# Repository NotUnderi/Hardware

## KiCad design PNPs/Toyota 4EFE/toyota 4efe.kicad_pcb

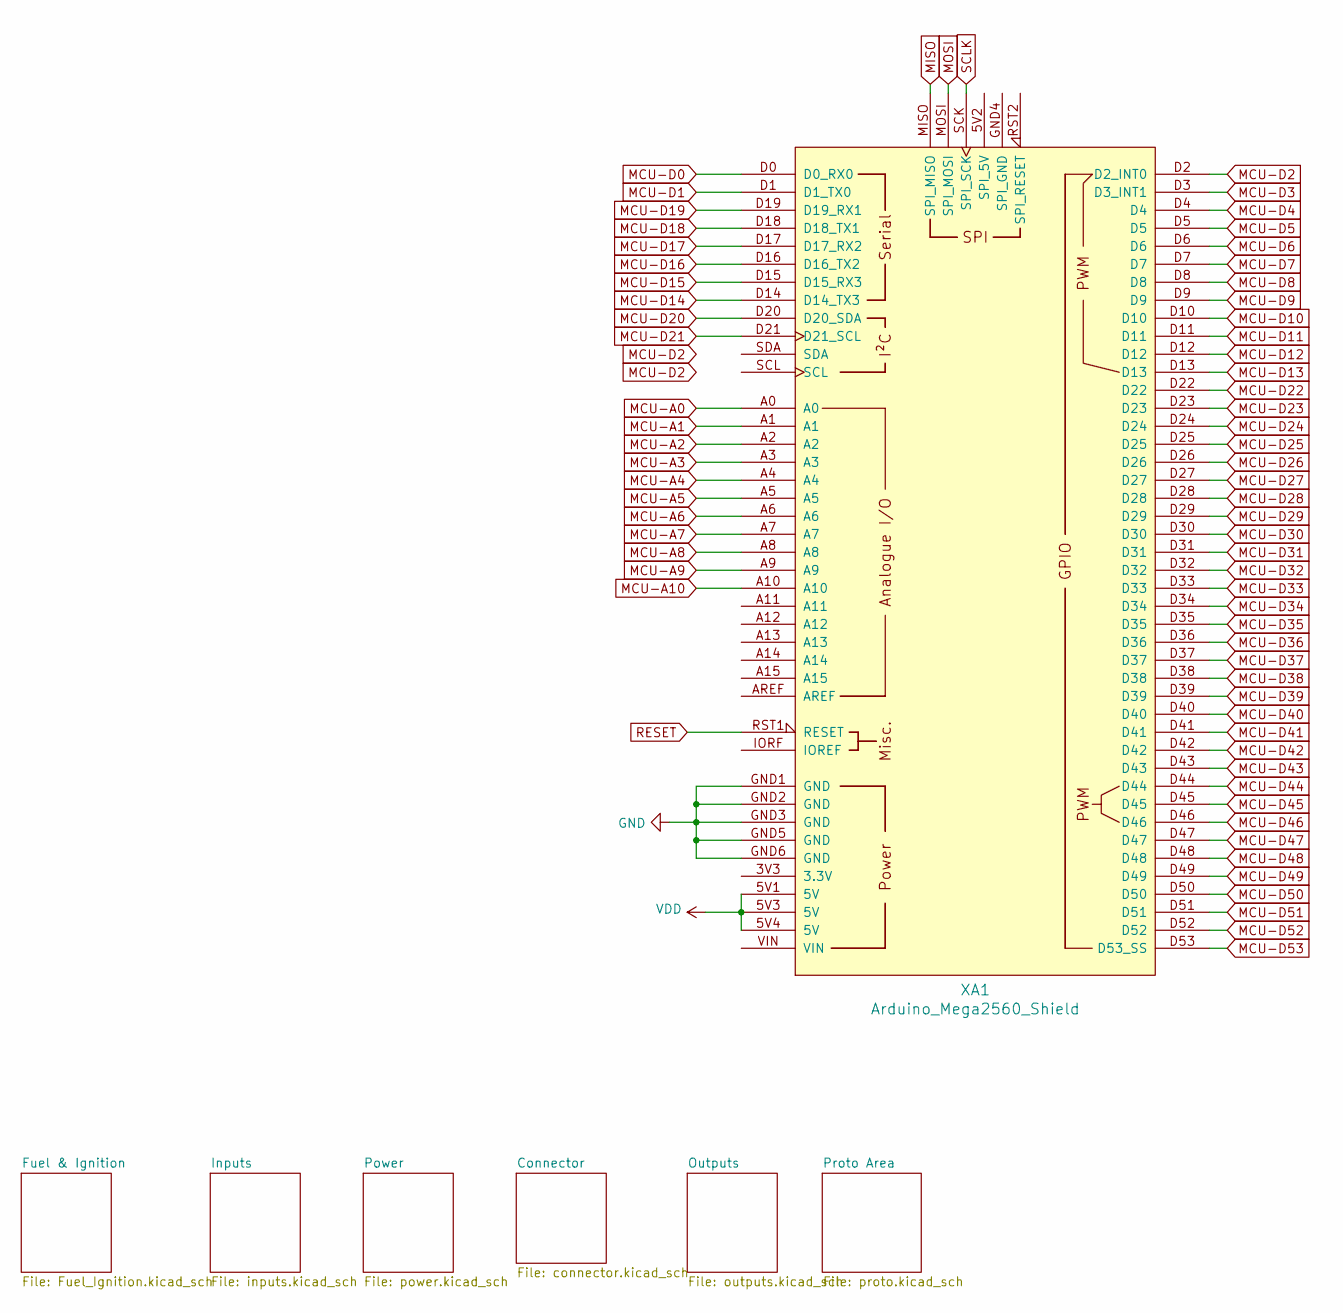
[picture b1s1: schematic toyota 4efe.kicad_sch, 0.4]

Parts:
XA1: Arduino_Mega2560_Shield; Arduino_Mega2560_R3_Shield

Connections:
ADC-Clamp-1: XA1.A4; also elsewhere on the board
ADC-Clamp-2: XA1.A3; also elsewhere on the board
ADC-Clamp-3: XA1.A1; also elsewhere on the board
ADC-Clamp-4: XA1.A2; also elsewhere on the board
ADC-Clamp-5: XA1.A0; also elsewhere on the board
ADC-Clamp-6: XA1.A8; also elsewhere on the board
ADC-Clamp-8: XA1.D18 (D18_TX1); also elsewhere on the board
ADC-Clamp-9: XA1.D19 (D19_RX1); also elsewhere on the board
GND: XA1.GND1 (GND), XA1.GND2 (GND), XA1.GND3 (GND), XA1.GND5 (GND), XA1.GND6 (GND); also elsewhere on the board
MCU-A5: XA1.A5; also elsewhere on the board
MCU-A6: XA1.A6
MCU-A7: XA1.A7
MCU-A9: XA1.A9
MCU-A10: XA1.A10
MCU-D0: XA1.D0 (D0_RX0)
MCU-D1: XA1.D1 (D1_TX0)
MCU-D2: XA1.D2 (D2_INT0)
MCU-D3: XA1.D3 (D3_INT1)
MCU-D4: XA1.D4; also elsewhere on the board
MCU-D5: XA1.D5; also elsewhere on the board
MCU-D6: XA1.D6; also elsewhere on the board
MCU-D7: XA1.D7; also elsewhere on the board
MCU-D8: XA1.D8; also elsewhere on the board
MCU-D9: XA1.D9; also elsewhere on the board
MCU-D10: XA1.D10
MCU-D11: XA1.D11
MCU-D12: XA1.D12
MCU-D13: XA1.D13
MCU-D14: XA1.D14 (D14_TX3)
MCU-D15: XA1.D15 (D15_RX3)
MCU-D16: XA1.D16 (D16_TX2); also elsewhere on the board
MCU-D17: XA1.D17 (D17_RX2); also elsewhere on the board
MCU-D20: XA1.D20 (D20_SDA)
MCU-D21: XA1.D21 (D21_SCL)
MCU-D22: XA1.D22
MCU-D23: XA1.D23
MCU-D24: XA1.D24; also elsewhere on the board
MCU-D25: XA1.D25
MCU-D26: XA1.D26
MCU-D27: XA1.D27
MCU-D28: XA1.D28
MCU-D29: XA1.D29
MCU-D30: XA1.D30
MCU-D31: XA1.D31
MCU-D32: XA1.D32
MCU-D33: XA1.D33
MCU-D34: XA1.D34
MCU-D35: XA1.D35
MCU-D36: XA1.D36
MCU-D37: XA1.D37
MCU-D38: XA1.D38; also elsewhere on the board
MCU-D39: XA1.D39
MCU-D40: XA1.D40; also elsewhere on the board
MCU-D41: XA1.D41
MCU-D42: XA1.D42
MCU-D43: XA1.D43
MCU-D44: XA1.D44
MCU-D45: XA1.D45
MCU-D46: XA1.D46
MCU-D47: XA1.D47; also elsewhere on the board
MCU-D48: XA1.D48
MCU-D49: XA1.D49
MCU-D50: XA1.D50
MCU-D51: XA1.D51
MCU-D52: XA1.D52
MCU-D53: XA1.D53 (D53_SS)
RESET: XA1.RST1 (RESET); also elsewhere on the board
VDD: XA1.5V1 (5V), XA1.5V3 (5V), XA1.5V4 (5V); also elsewhere on the board

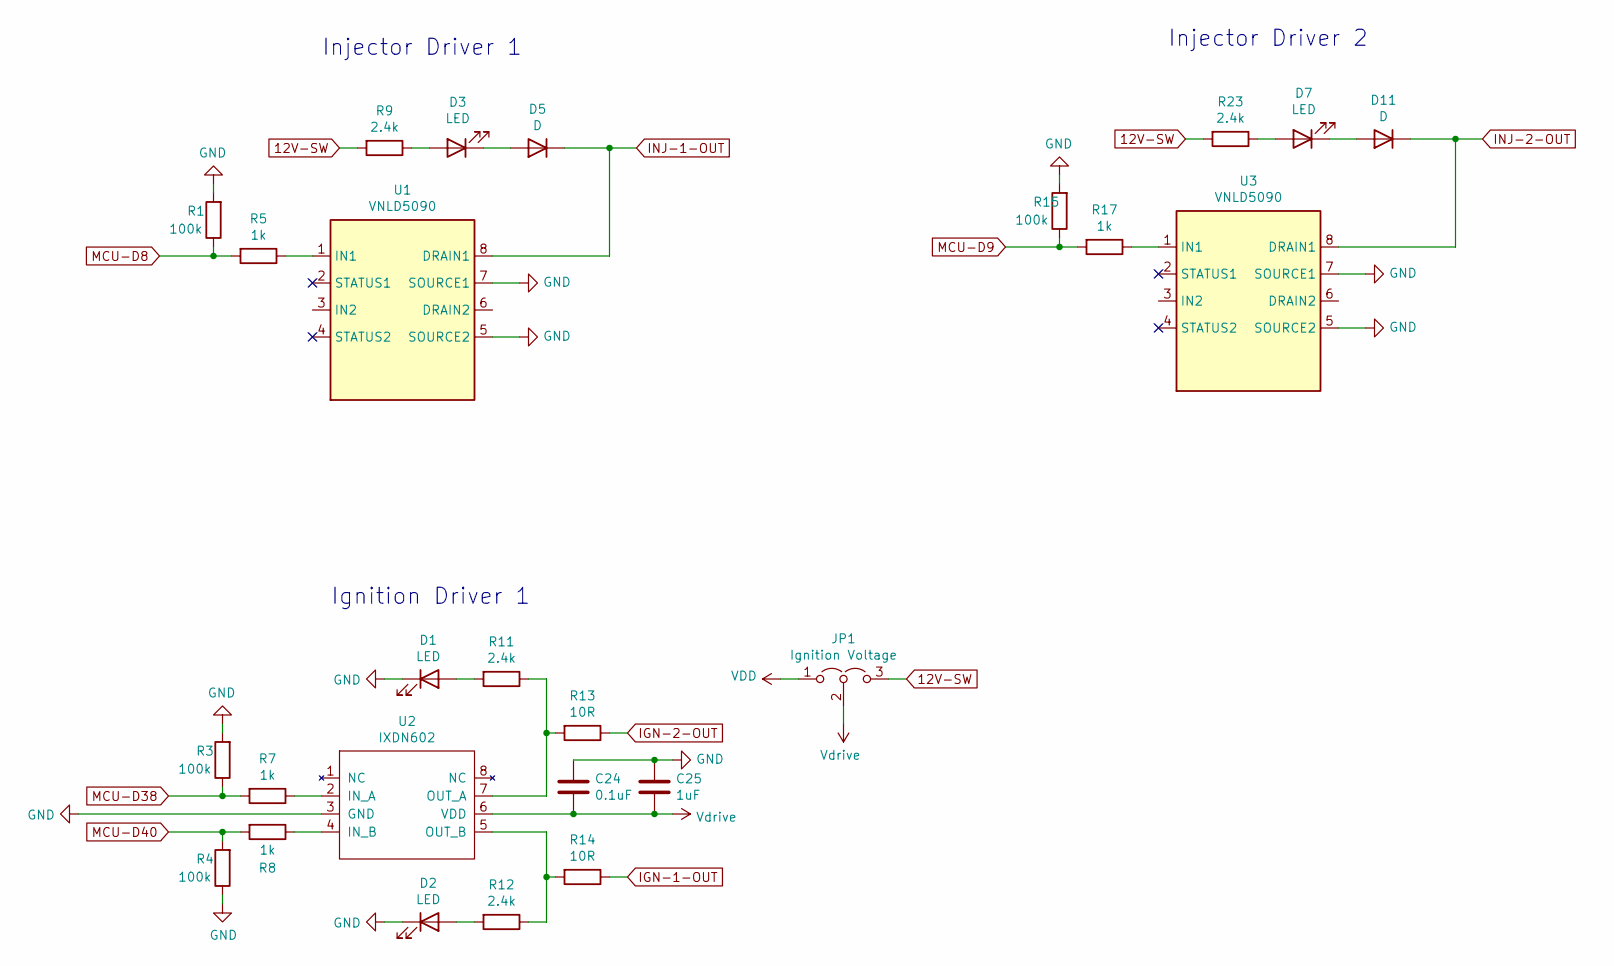
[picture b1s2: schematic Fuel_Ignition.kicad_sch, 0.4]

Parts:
C24: 0.1uF; C_0805_2012Metric; Manufacturer_Part_Number CC0805KRX7R9BB104; Digikey Part Number 311-1140-1-ND
C25: 1uF; C_0805_2012Metric; Manufacturer_Part_Number CC0805KKX7R7BB105; Digikey Part Number 311-1365-1-ND
D1, D2, D3, D7: LED; LED_0805_2012Metric; Manufacturer_Part_Number LH R974-LP-1; Digikey Part Number 475-1415-1-ND
D5, D11: D; D_SOD-323; Manufacturer_Part_Number 1N4448WX-TP; Digikey Part Number 1N4448WXTPMSCT-ND
JP1: Ignition Voltage; PinHeader_1x03_P2.54mm_Vertical; Manufacturer_Part_Number M20-9990345; Digikey Part Number 952-2263-ND
R1, R3, R4, R15: 100k; R_0805_2012Metric; Manufacturer_Part_Number RC0805FR-07100KL; Digikey Part Number 311-100KCRCT-ND
R5, R7, R8, R17: 1k; R_0805_2012Metric; Manufacturer_Part_Number RC0805FR-071KL; Digikey Part Number 311-1.00KCRCT-ND
R9, R11, R12, R23: 2.4k; R_0805_2012Metric; Manufacturer_Part_Number RC0805FR-072K4L; Digikey Part Number 311-2.40KCRCT-ND
R13, R14: 10R; R_1206_3216Metric; Manufacturer_Part_Number RC1206FR-0710RL; Digikey Part Number 311-10.0FRCT-ND
U1, U3: VNLD5090; SOIC-8_3.9x4.9mm_P1.27mm; Manufacturer_Part_Number VNLD5090-E; Digikey Part Number 497-18682-ND
U2: IXDN602; SOIC-8_3.9x4.9mm_P1.27mm; Manufacturer_Part_Number IXDN602SIATR; Digikey Part Number 212-IXDN602SIACT-ND

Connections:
12V-SW: JP1.3 (B), R9.2, R23.2; also elsewhere on the board
GND: C24.1, C25.1, D1.1 (K), D2.1 (K), R1.2, R3.2, R4.1, R15.2, U1.5 (SOURCE2), U1.7 (SOURCE1), U2.3 (GND), U3.5 (SOURCE2), U3.7 (SOURCE1); also elsewhere on the board
IGN-1-OUT: R14.1; also elsewhere on the board
IGN-2-OUT: R13.1; also elsewhere on the board
INJ-1-OUT: D5.1 (K), U1.8 (DRAIN1); also elsewhere on the board
INJ-2-OUT: D11.1 (K), U3.8 (DRAIN1); also elsewhere on the board
MCU-D8: R1.1, R5.2; also elsewhere on the board
MCU-D9: R15.1, R17.2; also elsewhere on the board
MCU-D38: R3.1, R7.2; also elsewhere on the board
MCU-D40: R4.2, R8.2; also elsewhere on the board
unnamed: D1.2 (A), R11.2
unnamed: D2.2 (A), R12.2
unnamed: D3.2 (A), R9.1
unnamed: D3.1 (K), D5.2 (A)
unnamed: D7.2 (A), R23.1
unnamed: D7.1 (K), D11.2 (A)
unnamed: R5.1, U1.1 (IN1)
unnamed: R7.1, U2.2 (IN_A)
unnamed: R8.1, U2.4 (IN_B)
unnamed: R11.1, R13.2, U2.7 (OUT_A)
unnamed: R12.1, R14.2, U2.5 (OUT_B)
unnamed: R17.1, U3.1 (IN1)
VDD: JP1.1 (A); also elsewhere on the board
Vdrive: C24.2, C25.2, JP1.2 (C), U2.6 (VDD)

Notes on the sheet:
Injector Driver 1
Ignition Driver 1
Injector Driver 2

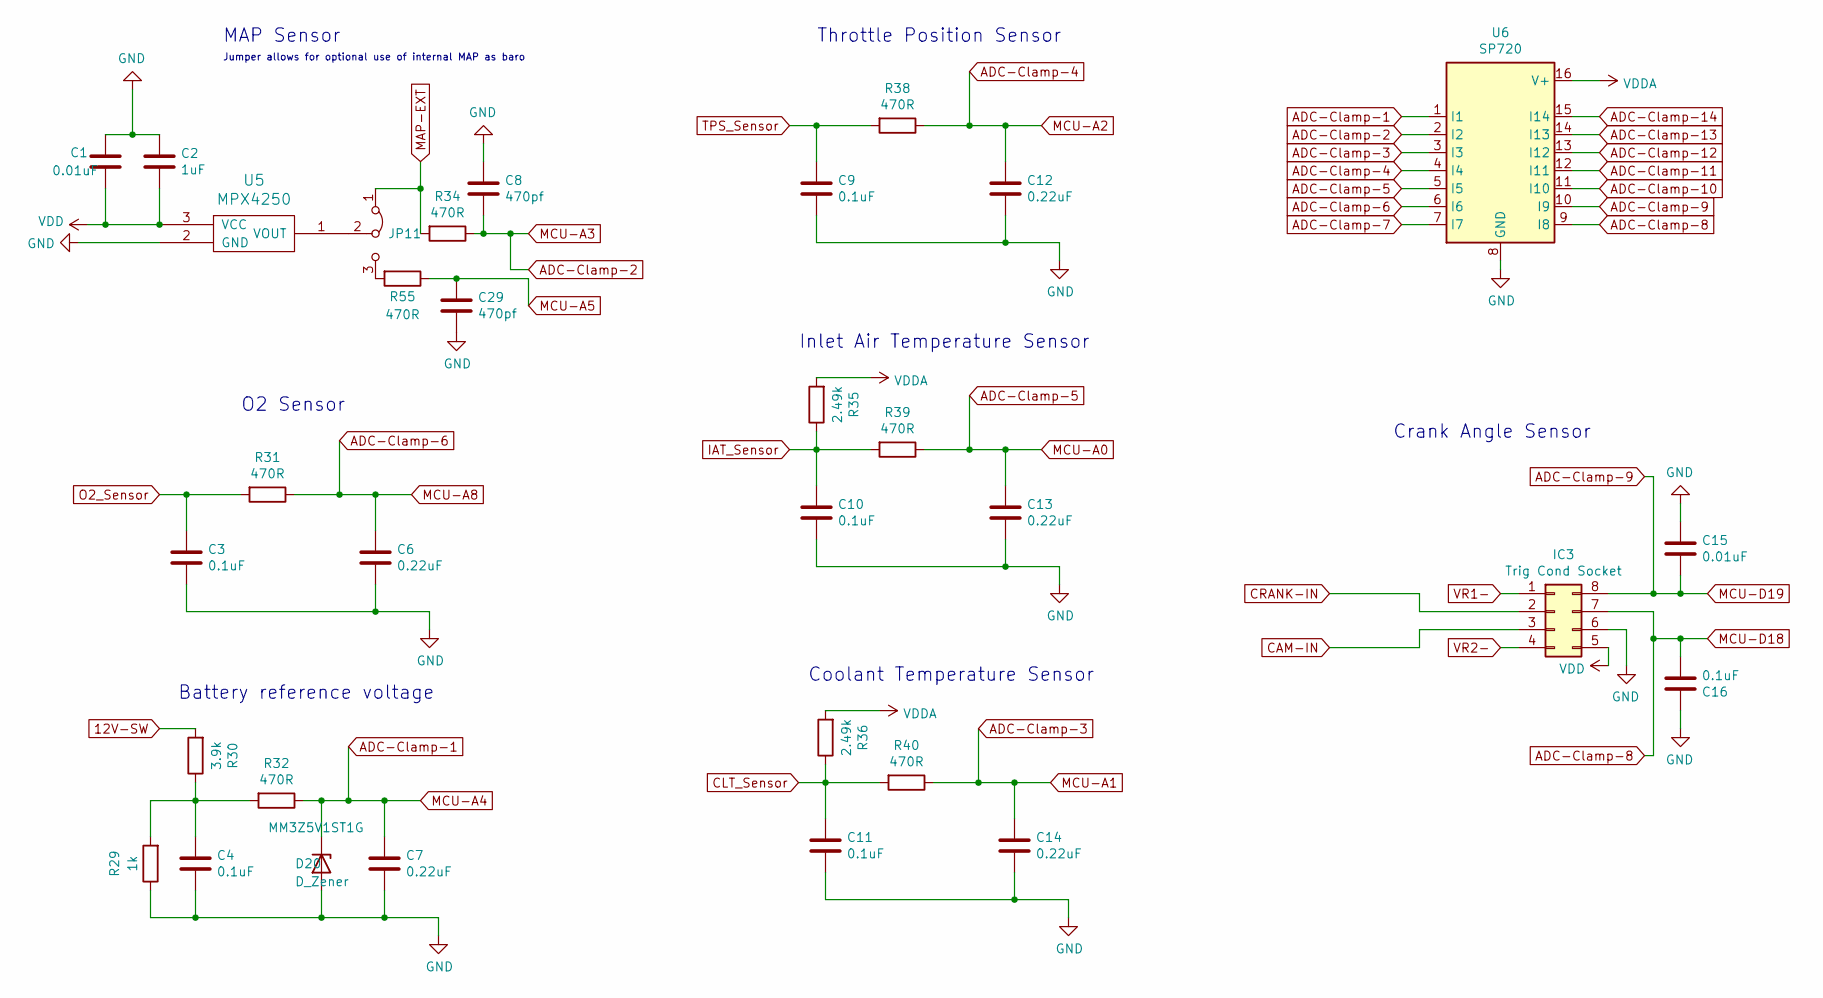
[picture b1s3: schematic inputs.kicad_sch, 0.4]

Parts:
C1, C15: 0.01uF; C_0805_2012Metric; Manufacturer_Part_Number CC0805KRX7R9BB103; Digikey Part Number 311-1136-1-ND
C2: 1uF; C_0805_2012Metric; Manufacturer_Part_Number CC0805KKX7R7BB105; Digikey Part Number 311-1365-1-ND
C3, C4, C9, C10, C11, C16: 0.1uF; C_0805_2012Metric; Manufacturer_Part_Number CC0805KRX7R9BB104; Digikey Part Number 311-1140-1-ND
C6, C7, C12, C13, C14: 0.22uF; C_0805_2012Metric; Manufacturer_Part_Number CL21B224KOCNNNC; Digikey Part Number 1276-1284-1-ND
C8, C29: 470pf; C_0805_2012Metric; Manufacturer_Part_Number CC0805KRX7R9BB471; Digikey Part Number 311-1124-1-ND
D20: D_Zener; D_SOD-323; Part # MM3Z5V1ST1G; Digikey Part Number MM3Z5V1ST1GOSCT-ND
IC3: Trig Cond Socket; DIP-8_W7.62mm_Socket
JP11: Jumper_3_Bridged12; SolderJumper-3_P1.3mm_Bridged12_RoundedPad1.0x1.5mm
R29: 1k; R_0805_2012Metric; Manufacturer_Part_Number RC0805FR-071KL; Digikey Part Number 311-1.00KCRCT-ND
R30: 3.9k; R_0805_2012Metric; Manufacturer_Part_Number RC0805FR-073K9L; Digikey Part Number 311-3.90KCRCT-ND
R31, R32, R34, R38, R39, R40, R55: 470R; R_0805_2012Metric; Manufacturer_Part_Number ERJ-6ENF4700V; Digikey Part Number P470CCT-ND
R35, R36: 2.49k; R_0805_2012Metric; Manufacturer_Part_Number RT0805BRD072K49L; Digikey Part Number YAG1854CT-ND
U5: MPX4250; MPX5700ASX; Manufacturer_Part_Number MPX4250AP; Digikey Part Number MPX4250AP-ND
U6: SP720; SOIC-16_3.9x9.9mm_P1.27mm; Manufacturer_Part_Number SP720ABTG; Digikey Part Number F3162CT-ND

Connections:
12V-SW: R30.2; also elsewhere on the board
ADC-Clamp-1: C7.1, D20.1 (K), R32.1, U6.1 (I1); also elsewhere on the board
ADC-Clamp-2: C8.2, R34.1, U6.2 (I2); also elsewhere on the board
ADC-Clamp-3: C14.1, R40.1, U6.3 (I3); also elsewhere on the board
ADC-Clamp-4: C12.1, R38.1, U6.4 (I4); also elsewhere on the board
ADC-Clamp-5: C13.1, R39.1, U6.5 (I5); also elsewhere on the board
ADC-Clamp-6: C6.1, R31.1, U6.6 (I6); also elsewhere on the board
ADC-Clamp-7: U6.7 (I7)
ADC-Clamp-8: C16.2, IC3.7, U6.9 (I8); also elsewhere on the board
ADC-Clamp-9: C15.2, IC3.8, U6.10 (I9); also elsewhere on the board
ADC-Clamp-10: U6.11 (I10)
ADC-Clamp-11: U6.12 (I11)
ADC-Clamp-12: U6.13 (I12)
ADC-Clamp-13: U6.14 (I13)
ADC-Clamp-14: U6.15 (I14)
CAM-IN: IC3.3
CLT_Sensor: C11.1, R36.1, R40.2; also elsewhere on the board
CRANK-IN: IC3.2; also elsewhere on the board
GND: C1.1, C2.1, C3.2, C4.2, C6.2, C7.2, C8.1, C9.2, C10.2, C11.2, C12.2, C13.2, C14.2, C15.1, C16.1, C29.2, D20.2 (A), IC3.6, R29.1, U5.2 (GND), U6.8 (GND); also elsewhere on the board
IAT_Sensor: C10.1, R35.1, R39.2; also elsewhere on the board
MAP-EXT: JP11.1 (A), R34.2; also elsewhere on the board
MCU-A5: C29.1, R55.1; also elsewhere on the board
unnamed: C4.1, R29.2, R30.1, R32.2
unnamed: JP11.3 (B), R55.2
unnamed: JP11.2 (C), U5.1 (VOUT)
O2_Sensor: C3.1, R31.2; also elsewhere on the board
TPS_Sensor: C9.1, R38.2; also elsewhere on the board
VDD: C1.2, C2.2, IC3.5, U5.3 (VCC); also elsewhere on the board
VDDA: R35.2, R36.2, U6.16 (V+); also elsewhere on the board
VR1-: IC3.1; also elsewhere on the board
VR2-: IC3.4

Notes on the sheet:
Inlet Air Temperature Sensor
Battery reference voltage
MAP Sensor
Coolant Temperature Sensor
Throttle Position Sensor
O2 Sensor
Jumper allows for optional use of internal MAP as baro
Crank Angle Sensor

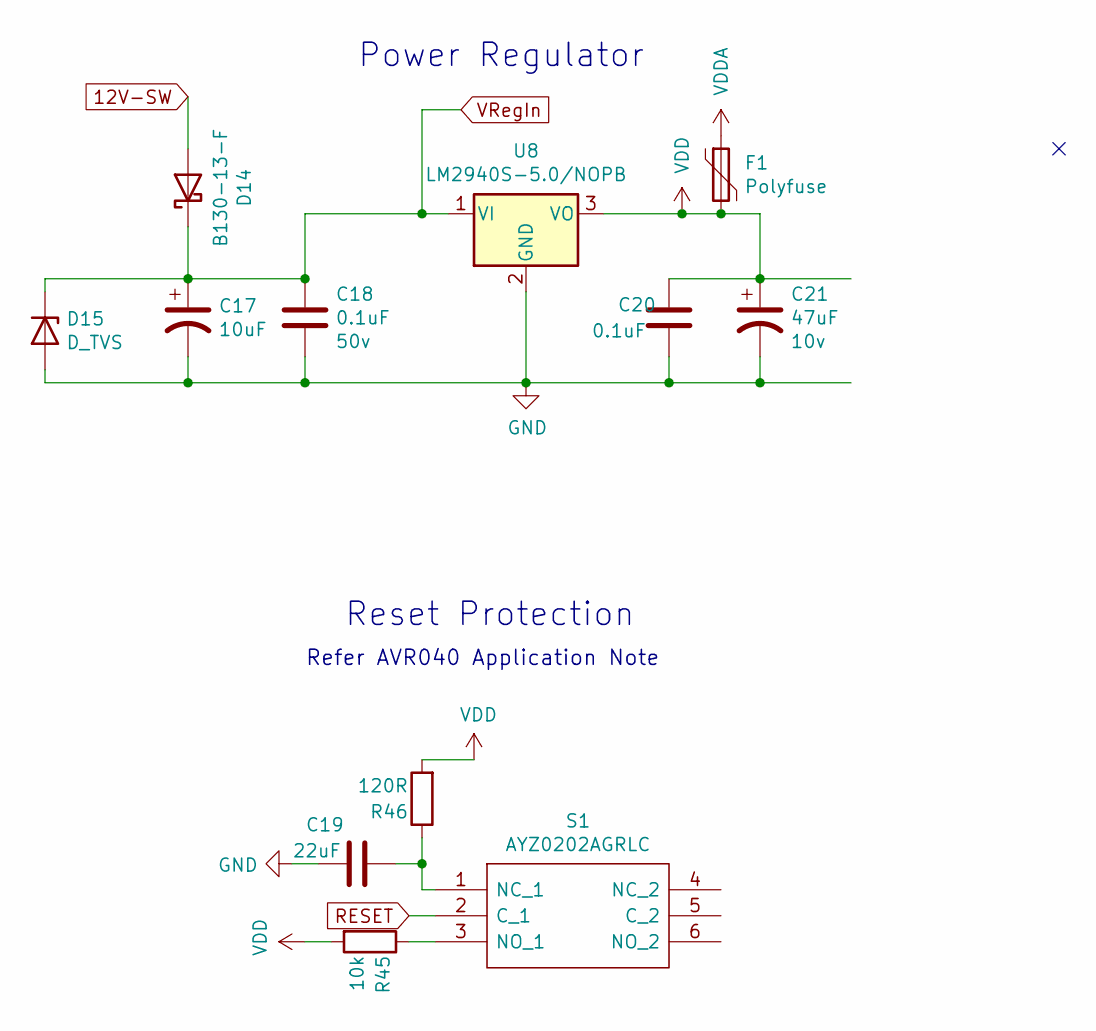
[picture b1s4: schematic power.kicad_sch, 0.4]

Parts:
C17: 10uF; CP_EIA-7343-31_Kemet-D; Voltage 35v; Manufacturer_Part_Number T491D106K050AT; Digikey Part Number 399-8361-1-ND
C18: 0.1uF; C_0805_2012Metric; Voltage 50v; Manufacturer_Part_Number CC0805KRX7R9BB104; Digikey Part Number 311-1140-1-ND
C19: 22uF; C_0805_2012Metric; Manufacturer_Part_Number CL21A226KQCLRNC; Digikey Part Number 1276-6687-1-ND
C20: 0.1uF; C_0805_2012Metric; Manufacturer_Part_Number CC0805KRX7R9BB104; Digikey Part Number 311-1140-1-ND
C21: 47uF; CP_EIA-3528-21_Kemet-B; Voltage 10v; Manufacturer_Part_Number TAJB476K006RNJ; Digikey Part Number 478-1692-1-ND
D14: B130-13-F; D_SMA; Manufacturer_Part_Number B130-13-F; Digikey Part Number B130-FDICT-ND
D15: D_TVS; D_SMB; Manufacturer_Part_Number SMBJ40A-Q; Digikey Part Number SMBJ40A-QCT-ND
F1: Polyfuse; Fuse_1812_4532Metric; Manufacturer_Part_Number 0ZCC0050FF2C; Digikey Part Number 507-1361-1-ND
R45: 10k; R_0805_2012Metric; Manufacturer_Part_Number RC0805JR-0710KL; Digikey Part Number 311-10KARCT-ND
R46: 120R; R_0805_2012Metric; Manufacturer_Part_Number RC0805FR-07120RL; Digikey Part Number 311-120CRCT-ND
S1: AYZ0202AGRLC; Manufacturer_Part_Number AYZ0202AGRLC; Digikey Part Number 401-2013-1-ND
U8: LM2940S-5.0/NOPB; TO-263-3_TabPin2; Manufacturer_Part_Number LM2940S-5.0/NOPB; Digikey Part Number LM2940S-5.0/NOPB-ND

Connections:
12V-SW: D14.2 (A); also elsewhere on the board
GND: C17.2, C18.2, C19.2, C20.2, C21.2, D15.2 (A), U8.2 (GND); also elsewhere on the board
unnamed: C19.1, R46.1, S1.1 (NC_1)
unnamed: R45.1, S1.3 (NO_1)
RESET: S1.2 (C_1); also elsewhere on the board
VDD: C20.1, C21.1, F1.2, R45.2, R46.2, U8.3 (VO); also elsewhere on the board
VDDA: F1.1; also elsewhere on the board
VRegIn: C17.1, C18.1, D14.1 (K), D15.1 (K), U8.1 (VI)

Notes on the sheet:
Power Regulator
Refer AVR040 Application Note
Reset Protection

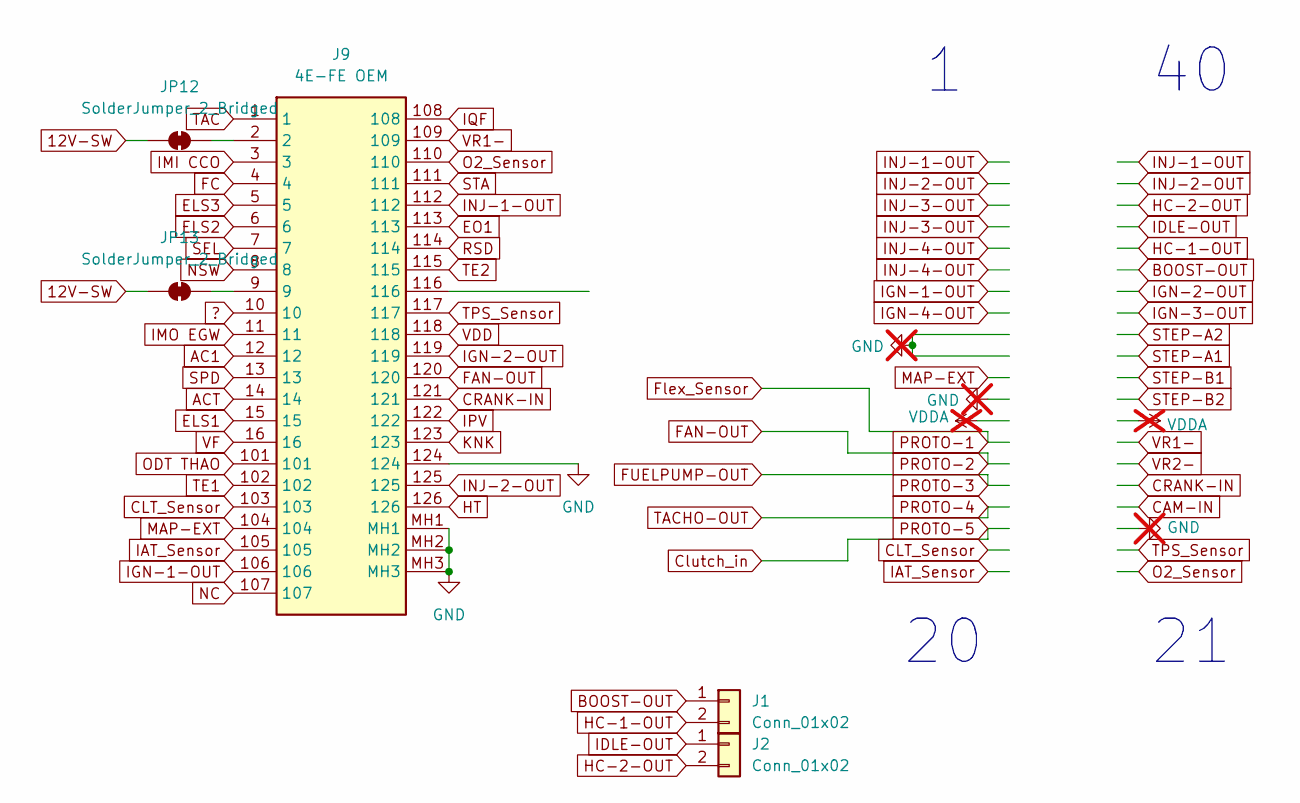
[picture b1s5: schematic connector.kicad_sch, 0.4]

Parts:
J1, J2: Conn_01x02; PinHeader_1x02_P2.54mm_Vertical
J9: 4E-FE OEM; Mouser Part Number 571-175446-6
JP12, JP13: SolderJumper_2_Bridged

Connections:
12V-SW: JP12.1 (A), JP13.1 (A); also elsewhere on the board
?: J9.10
AC1: J9.12
ACT: J9.14
BOOST-OUT: J1.1; also elsewhere on the board
CLT_Sensor: J9.103; also elsewhere on the board
CRANK-IN: J9.121; also elsewhere on the board
ELS1: J9.15
ELS2: J9.6
ELS3: J9.5
EO1: J9.113
FAN-OUT: J9.120; also elsewhere on the board
FC: J9.4
GND: J9.124, J9.MH1, J9.MH2, J9.MH3; also elsewhere on the board
HC-1-OUT: J1.2; also elsewhere on the board
HC-2-OUT: J2.2; also elsewhere on the board
HT: J9.126
IAT_Sensor: J9.105; also elsewhere on the board
IDLE-OUT: J2.1; also elsewhere on the board
IGN-1-OUT: J9.106; also elsewhere on the board
IGN-2-OUT: J9.119; also elsewhere on the board
IMI CCO: J9.3
IMO EGW: J9.11
INJ-1-OUT: J9.112; also elsewhere on the board
INJ-2-OUT: J9.125; also elsewhere on the board
IPV: J9.122
IQF: J9.108
KNK: J9.123
MAP-EXT: J9.104; also elsewhere on the board
NC: J9.107
NSW: J9.8
unnamed: J9.2, JP12.2 (B)
unnamed: J9.9, JP13.2 (B)
O2_Sensor: J9.110; also elsewhere on the board
ODT THAO: J9.101
RSD: J9.114
SEL: J9.7
SPD: J9.13
STA: J9.111
TAC: J9.1
TE1: J9.102
TE2: J9.115
TPS_Sensor: J9.117; also elsewhere on the board
VDD: J9.118; also elsewhere on the board
VF: J9.16
VR1-: J9.109; also elsewhere on the board

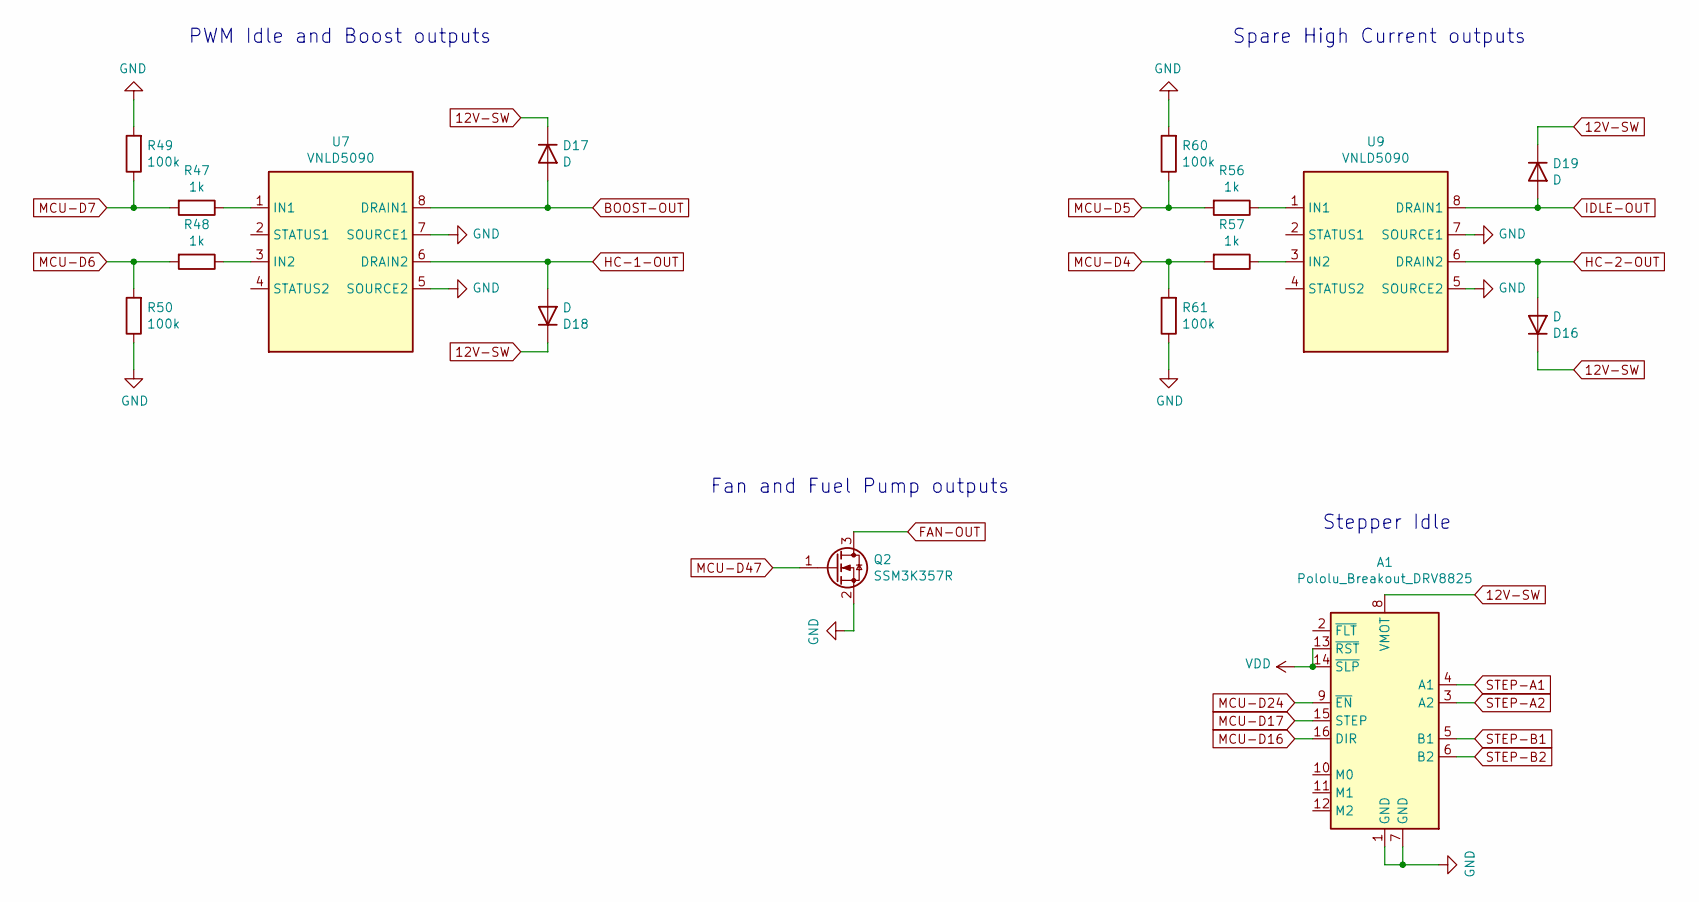
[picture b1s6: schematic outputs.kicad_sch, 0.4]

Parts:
A1: Pololu_Breakout_DRV8825; Pololu_Breakout-16_15.2x20.3mm
D16, D17, D18, D19: D; D_SOD-123F; Manufacturer_Part_Number S110FA; Digikey Part Number S110FACT-ND
Q2: SSM3K357R; SOT-23; Manufacturer_Part_Number SSM3K357R; Digikey Part Number SSM3K357RLFCT-ND
R47, R48, R56, R57: 1k; R_0805_2012Metric; Manufacturer_Part_Number RC0805FR-071KL; Digikey Part Number 311-1.00KCRCT-ND
R49, R50, R60, R61: 100k; R_0805_2012Metric; Manufacturer_Part_Number RC0805FR-07100KL; Digikey Part Number 311-100KCRCT-ND
U7, U9: VNLD5090; SOIC-8_3.9x4.9mm_P1.27mm; Manufacturer_Part_Number VNLD5090-E; Digikey Part Number 497-18682-ND

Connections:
12V-SW: A1.8 (VMOT), D16.1 (K), D17.1 (K), D18.1 (K), D19.1 (K); also elsewhere on the board
BOOST-OUT: D17.2 (A), U7.8 (DRAIN1); also elsewhere on the board
FAN-OUT: Q2.3 (D); also elsewhere on the board
GND: A1.1 (GND), A1.7 (GND), Q2.2 (S), R49.2, R50.1, R60.2, R61.1, U7.5 (SOURCE2), U7.7 (SOURCE1), U9.5 (SOURCE2), U9.7 (SOURCE1); also elsewhere on the board
HC-1-OUT: D18.2 (A), U7.6 (DRAIN2); also elsewhere on the board
HC-2-OUT: D16.2 (A), U9.6 (DRAIN2); also elsewhere on the board
IDLE-OUT: D19.2 (A), U9.8 (DRAIN1); also elsewhere on the board
MCU-D4: R57.2, R61.2; also elsewhere on the board
MCU-D5: R56.2, R60.1; also elsewhere on the board
MCU-D6: R48.2, R50.2; also elsewhere on the board
MCU-D7: R47.2, R49.1; also elsewhere on the board
MCU-D16: A1.16 (DIR); also elsewhere on the board
MCU-D17: A1.15 (STEP); also elsewhere on the board
MCU-D24: A1.9 (~EN); also elsewhere on the board
MCU-D47: Q2.1 (G); also elsewhere on the board
unnamed: R47.1, U7.1 (IN1)
unnamed: R48.1, U7.3 (IN2)
unnamed: R56.1, U9.1 (IN1)
unnamed: R57.1, U9.3 (IN2)
STEP-A1: A1.4 (A1)
STEP-A2: A1.3 (A2)
STEP-B1: A1.5 (B1)
STEP-B2: A1.6 (B2)
VDD: A1.13 (~RST), A1.14 (~SLP); also elsewhere on the board

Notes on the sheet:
Stepper Idle
PWM Idle and Boost outputs
Fan and Fuel Pump outputs
Spare High Current outputs

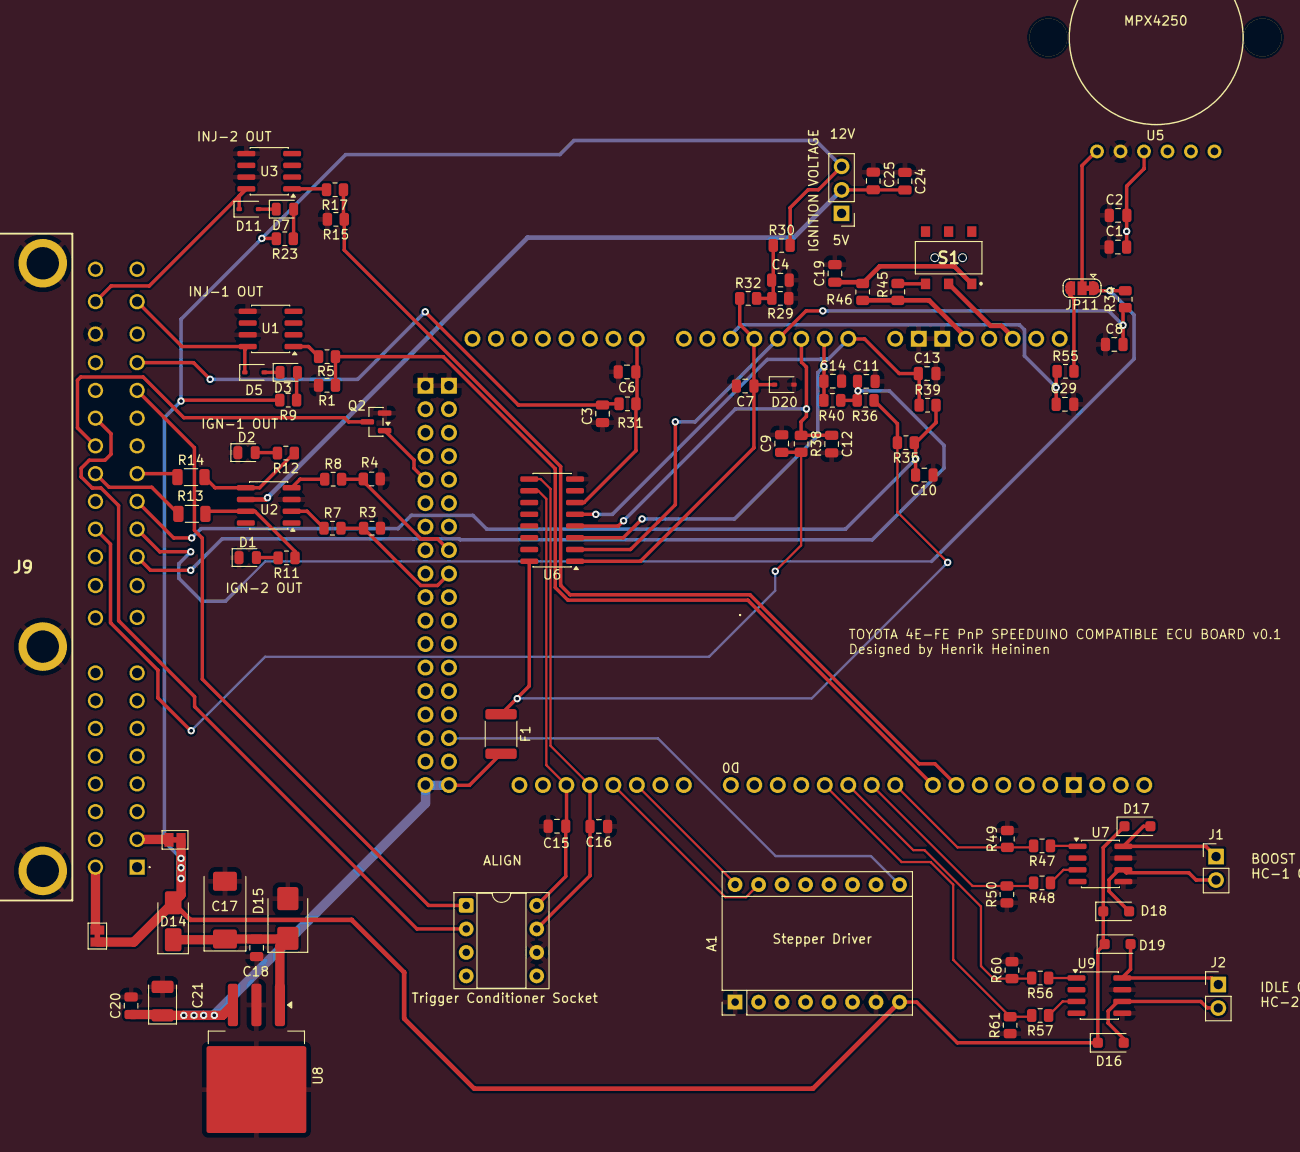
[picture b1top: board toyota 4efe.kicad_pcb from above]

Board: 4 copper layers, 92 parts (0 on the bottom side), 67 nets.

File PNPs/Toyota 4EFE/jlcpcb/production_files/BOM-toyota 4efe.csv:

Comment,Designator,Footprint,LCSC,Quantity
0.01uF,"C1,C15",C_0805_2012Metric,C1710,2
0.1uF,"C10,C11,C16,C18,C20,C24,C3,C4,C9",C_0805_2012Metric,C49678,9
0.22uF,"C12,C13,C14,C6,C7",C_0805_2012Metric,C5378,5
100k,"R1,R15,R3,R4,R49,R50,R60,R61",R_0805_2012Metric,C149504,8
10R,"R13,R14",R_1206_3216Metric,C17903,2
10k,R45,R_0805_2012Metric,C17414,1
10uF,C17,CP_EIA-7343-31_Kemet-D,C347556,1
120R,R46,R_0805_2012Metric,C17437,1
1k,"R17,R29,R47,R48,R5,R56,R57,R7,R8",R_0805_2012Metric,C17513,9
1uF,"C2,C25",C_0805_2012Metric,C28323,2
2.49k,"R35,R36",R_0805_2012Metric,C21237,2
2.4k,"R11,R12,R23,R9",R_0805_2012Metric,C17526,4
22uF,C19,C_0805_2012Metric,C45783,1
3.9k,R30,R_0805_2012Metric,C17614,1
470R,"R31,R32,R34,R38,R39,R40,R55",R_0805_2012Metric,C17710,7
470pf,"C29,C8",C_0805_2012Metric,C1743,2
47uF,C21,CP_EIA-3528-21_Kemet-B,C2158185,1
B130-13-F,D14,D_SMA,C2480,1
D,"D11,D5",D_SOD-323,C2128,2
D,"D16,D17,D18,D19",D_SOD-123F,C64898,4
D_TVS,D15,D_SMB,C2898533,1
D_Zener,D20,D_SOD-323,C12744,1
IXDN602,U2,SOIC-8_3.9x4.9mm_P1.27mm,C431679,1
LED,"D1,D2,D3,D7",LED_0805_2012Metric,C84256,4
LM2940S-5.0/NOPB,U8,TO-263-3_TabPin2,C133956,1
Polyfuse,F1,Fuse_1812_4532Metric,C20810,1
SP720,U6,SOIC-16_3.9x9.9mm_P1.27mm,C434726,1
SSM3K357R,Q2,SOT-23,C7369997,1
VNLD5090,"U1,U3,U7,U9",SOIC-8_3.9x4.9mm_P1.27mm,C222209,4
Pololu_Breakout_DRV8825,A1,Pololu_Breakout-16_15.2x20.3mm,,1
Arduino_Mega2560_Shield,XA1,Uno Shield,,1
MPX4250,U5,MPX5700ASX,,1

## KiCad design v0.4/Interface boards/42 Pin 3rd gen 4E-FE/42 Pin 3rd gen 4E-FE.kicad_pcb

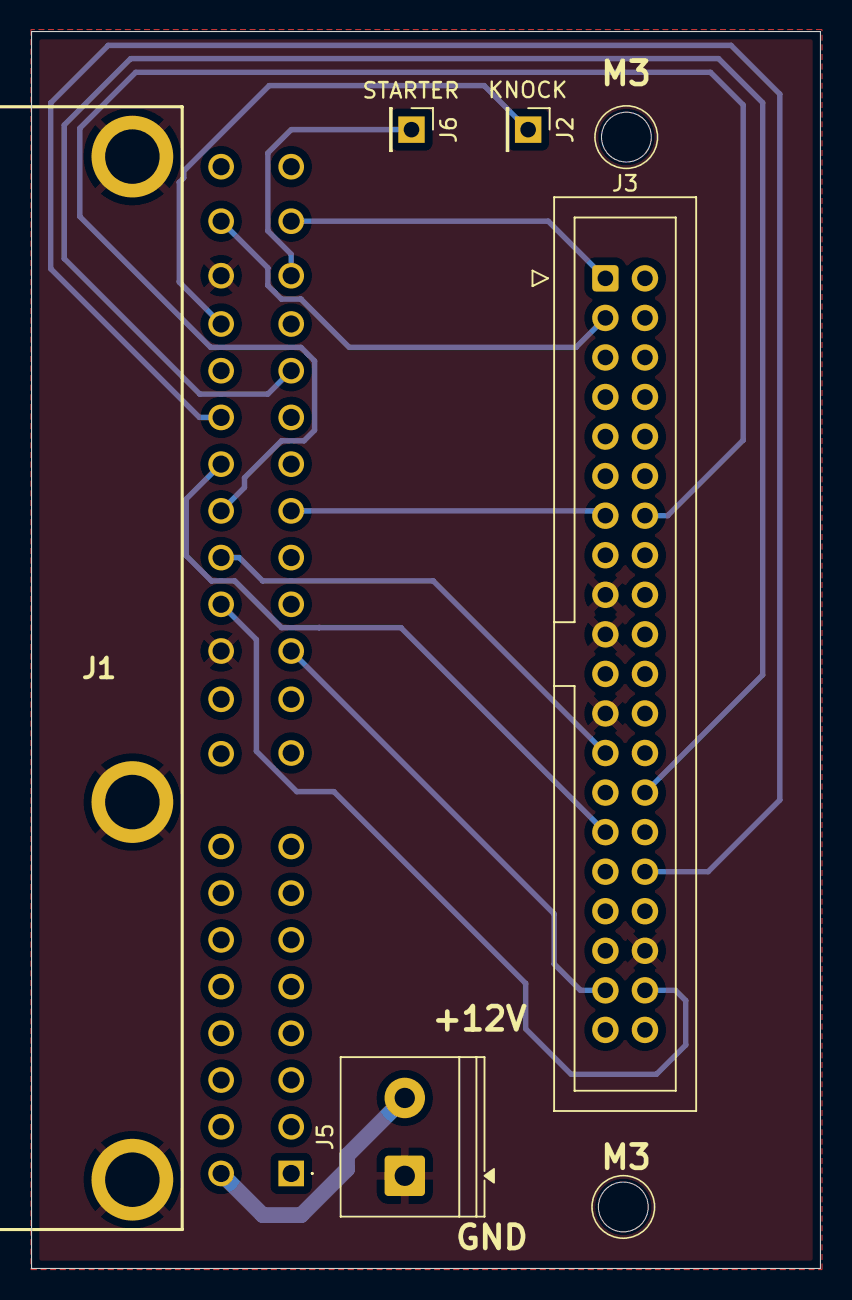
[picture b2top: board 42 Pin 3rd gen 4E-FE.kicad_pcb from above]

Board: 2 copper layers, 50.7 x 79.4 mm, 5 parts (0 on the bottom side), 14 nets.

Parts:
J1: 4E-FE OEM; 1754466
J2: KNOCK; PinHeader_1x01_P2.54mm_Vertical
J3: Speeduino; IDC-Header_2x20_P2.54mm_Vertical
J5: Conn_01x02; TerminalBlock_Phoenix_PT-1,5-2-5.0-H_1x02_P5.00mm_Horizontal
J6: STARTER; PinHeader_1x01_P2.54mm_Vertical

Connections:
#10: J1.112, J3.1, J3.2
#20: J1.125, J3.3, J3.4
+B: J1.9, J5.2
E1: J1.116, J1.124, J1.MH1, J1.MH2, J1.MH3, J3.17, J3.19, J3.23, J3.36, J5.1
FAN CF: J1.120, J3.29
IGT1: J1.106, J3.13
IGT2: J1.119, J3.14
KNK: J1.123, J2.1
NE: J1.121, J3.32
NE-: J1.109, J3.28
STA: J1.111, J6.1
THW: J1.103, J3.37
VCC: J1.118, J3.25
VTA: J1.117, J3.38

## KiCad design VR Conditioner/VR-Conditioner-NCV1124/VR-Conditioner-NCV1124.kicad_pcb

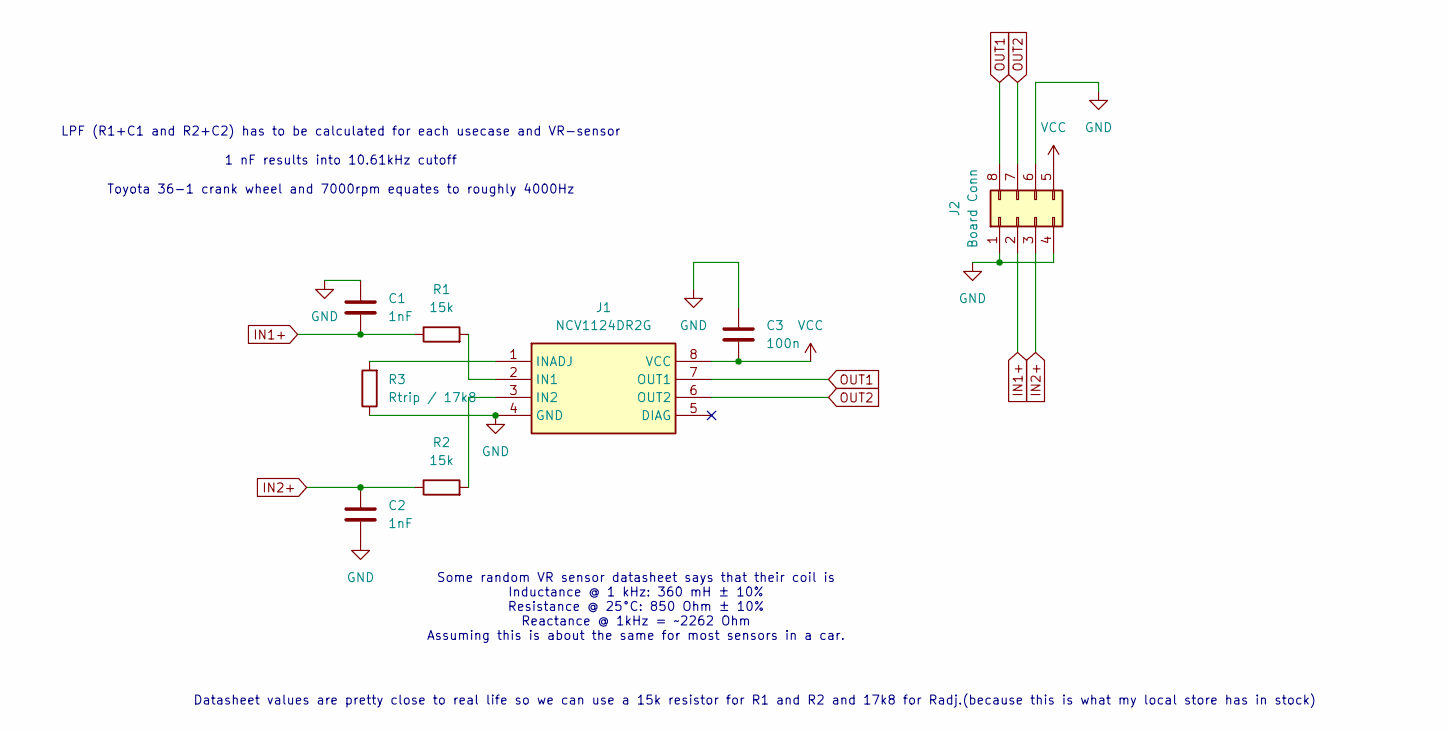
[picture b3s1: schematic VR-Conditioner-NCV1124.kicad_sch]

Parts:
C1, C2: 1nF; C_1206_3216Metric_Pad1.33x1.80mm_HandSolder
C3: 100n; C_1206_3216Metric_Pad1.33x1.80mm_HandSolder
J1: NCV1124DR2G; NCV7192D0R2G; Mouser Part Number 863-NCV1124DR2G
J2: Board Conn; DIP-8_W7.62mm_Socket_LongPads
R1, R2: 15k; R_Axial_DIN0207_L6.3mm_D2.5mm_P10.16mm_Horizontal
R3: Rtrip / 17k8; R_Axial_DIN0207_L6.3mm_D2.5mm_P10.16mm_Horizontal

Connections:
GND: C1.1, C2.2, C3.1, J1.4 (GND), J2.1, J2.4, J2.6, R3.1
IN1+: C1.2, J2.2, R1.1
IN2+: C2.1, J2.3, R2.1
unnamed: J1.2 (IN1), R1.2
unnamed: J1.3 (IN2), R2.2
unnamed: J1.1 (INADJ), R3.2
OUT1: J1.7 (OUT1), J2.8
OUT2: J1.6 (OUT2), J2.7
VCC: C3.2, J1.8 (VCC), J2.5

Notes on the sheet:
Datasheet values are pretty close to real life so we can use a 15k resistor for R1 and R2 and 17k8 for Radj.(because this is what my local store has in stock)
Some random VR sensor datasheet says that their coil is Inductance @ 1 kHz: 360 mH ± 10% Resistance @ 25°C: 850 Ohm ± 10% Reactance @ 1kHz = ~2262 Ohm Assuming this is about the same for most sensors in a car.
LPF (R1+C1 and R2+C2) has to be calculated for each usecase and VR-sensor 1 nF results into 10.61kHz cutoff Toyota 36-1 crank wheel and 7000rpm equates to roughly 4000Hz

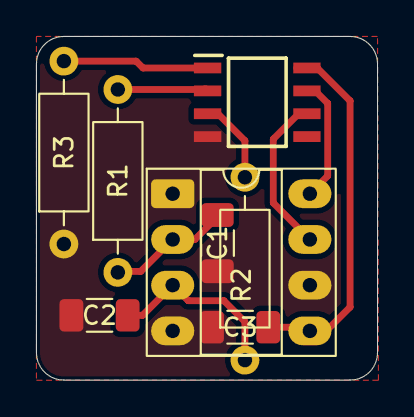
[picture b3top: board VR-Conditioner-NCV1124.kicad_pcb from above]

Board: 2 copper layers, 18.9 x 19.1 mm, 8 parts (0 on the bottom side), 9 nets.

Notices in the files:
DropBear/V2/DropBear.kicad_pcb:
© Josh Stewart
VR Conditioner/Latest/VR-Conditioner-MAX9926+reg.kicad_pcb:
(c)2021 Phill Rogers @ TechColab.co.je
VR Conditioner/VR-Conditioner-NCV1124/VR-Conditioner-NCV1124.kicad_pcb:
(c) 2026
parts and their libraries:
Copyright 2016 Accelerated Designs. All rights reserved.
